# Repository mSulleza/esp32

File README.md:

# ESP32 Smart AC Controller

An IR-based smart controller for air conditioners. An ESP32 **learns** your AC
remote's IR codes, **replays** them to drive the AC (power / mode / temperature /
fan speed), reads **temperature & humidity** from a BME280 sensor, and fires
**schedules** locally even when the internet is down. Everything is connected to
an **AWS IoT Core + Lambda + DynamoDB** backend so you can control and schedule
it from anywhere.

```
   ┌──────────────┐        IR (38 kHz)        ┌──────────────┐
   │  AC Remote   │ ─────capture (learn)────► │              │
   └──────────────┘                           │    ESP32     │
   ┌──────────────┐                           │  Controller  │
   │ Air          │ ◄──────replay (send)───── │              │
   │ Conditioner  │                           │  + BME280    │
   └──────────────┘                           └──────┬───────┘
                                                      │ MQTT / TLS
                                                      ▼
                                    ┌─────────────────────────────────┐
                                    │   AWS IoT Core ── IoT Rules      │
                                    │      │            │              │
                                    │   Lambda  ──  DynamoDB           │
                                    │      │                           │
                                    │   API Gateway (HTTP API) ── App  │
                                    └─────────────────────────────────┘
```

## Repository layout

| Path | What's inside |
|------|---------------|
| `docs/DESIGN.md`   | System architecture, data flow, MQTT topics, data model |
| `docs/HARDWARE.md` | Breadboard/prototype wiring (dev-board + modules) for quick bring-up |
| `hardware/`        | **Orderable integrated PCB**: schematic, PCBA BOM (LCSC), layout + JLCPCB fab/order steps |
| `docs/API.md`      | REST API + MQTT topic + Device Shadow contracts |
| `docs/COST.md`     | Cost breakdown, optimizations, and the billing guardrail |
| `firmware/`        | PlatformIO ESP32 firmware (IR learn/send, sensor, schedules, MQTT) |
| `backend/cdk/`     | AWS CDK infrastructure (IoT Core, Lambda, DynamoDB, API Gateway) |
| `backend/lambdas/` | Lambda function source (API, command publisher, schedule sync) |

## Quick start

1. **Hardware** — build the circuit in [`docs/HARDWARE.md`](docs/HARDWARE.md).
2. **Backend** — `cd backend/cdk && npm install && npx cdk deploy`. Note the
   IoT endpoint and API URL it prints, and download the device certificate.
3. **Firmware** — copy `firmware/src/secrets.example.h` to `secrets.h`, fill in
   Wi-Fi + IoT endpoint + certificates, then `cd firmware && pio run -t upload`.
4. **Learn your remote** — put the device in capture mode (button or API), point
   your AC remote at the receiver, and press each button to store the codes.
5. **Control & schedule** — use the REST API / app to send commands and create
   schedules.

See each `docs/` file for full detail. Status: **reference design + working
skeleton** — protocol decoding for your specific AC may need tuning (see
`docs/DESIGN.md` § "Generic / multi-brand strategy").

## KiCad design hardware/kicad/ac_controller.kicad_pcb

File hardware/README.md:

# Hardware — Integrated PCB (orderable)

This folder is the **manufacturable, integrated board**: a bare
**ESP32-WROOM-32E** with USB-C, USB-UART programming, an on-board 3.3 V
regulator, on-board BME280, an on-board **SMD IR receiver** (to learn your
remote) and an on-board **SMD IR emitter LED** (to send commands to the AC).
**Fully JLCPCB-PCBA assembled** — every part is SMD; the only through-hole pads
are the ESP32 thermal vias (reflowed) and the USB-C connector's anchor legs
(which JLC assembles). Nothing is left for you to hand-solder.

> Trade-off vs. the earlier external-LED design: the IR emitter is now an
> **on-board top-view LED**, so the **board itself must face the AC** (no aimable
> flying lead). That's the cost of full machine assembly.

> The breadboard/prototype wiring in [`../docs/HARDWARE.md`](../docs/HARDWARE.md)
> is the *quick bring-up* version using dev-board + modules. **This** folder is
> the integrated PCB you actually order. The firmware pin map is identical, so
> firmware needs no changes between the two.

## Files

| File | What it is |
|------|------------|
| [`kicad/ac_controller.kicad_pro`](kicad/ac_controller.kicad_pro) | KiCad project (open this) |
| [`kicad/ac_controller.kicad_sch`](kicad/ac_controller.kicad_sch) | **Real, openable KiCad 10 schematic.** ERC-validated: **0 errors** |
| [`kicad/ac_controller.pdf`](kicad/ac_controller.pdf) | Rendered schematic to eyeball without opening KiCad |
| [`kicad/ac_controller.net`](kicad/ac_controller.net) | Exported netlist (connectivity reference) |
| [`kicad/ac_controller.kicad_pcb`](kicad/ac_controller.kicad_pcb) | Board with **all footprints placed** (un-routed starting point; also the source of the 3D render) |
| [`kicad/board3d.png`](kicad/board3d.png) | **3D render** of the populated board |
| [`kicad/gen_schematic.py`](kicad/gen_schematic.py) | Generator for the schematic (reads your KiCad symbol libs) |
| [`kicad/gen_pcb.py`](kicad/gen_pcb.py) | Generator for the placed PCB / 3D render (uses the `pcbnew` Python API) |
| [`SCHEMATIC.md`](SCHEMATIC.md) | Human-readable schematic: every sub-circuit + net-by-net netlist |
| [`BOM.csv`](BOM.csv) | PCBA bill of materials with LCSC part numbers (Basic/Extended flagged) |
| [`LAYOUT.md`](LAYOUT.md) | Stackup, JLCPCB design rules, placement, routing, **Gerber export + ordering steps** |
| [`LAYOUT_AUTOMATION.md`](LAYOUT_AUTOMATION.md) | **Researched + tested** free/headless place-&-route pipeline (pcbnew placer + Freerouting) |
| [`kicad/build_board.py`](kicad/build_board.py) | Heuristic placer: nets the board + clusters parts by subsystem |
| [`kicad/run_pipeline.sh`](kicad/run_pipeline.sh) | One-shot place → DSN → Freerouting → SES → DRC |
| [`kicad/placed.kicad_pcb`](kicad/placed.kicad_pcb) · `placed_top.png` | Subsystem-placed board, **68×42 mm** — fixes the grid layout |
| [`kicad/routed.kicad_pcb`](kicad/routed.kicad_pcb) · `routed_top.png` | **Fully autorouted** (0 unconnected) |
| [`kicad/finished.kicad_pcb`](kicad/finished.kicad_pcb) · `finished_top.png` · `finished_3d.png` | **Finished board**: GND pour + antenna keep-out. **68×42 mm, DRC fully clean (0 of everything)**. |
| [`kicad/finish_board.py`](kicad/finish_board.py) | Adds the GND pour and fills zones |
| [`kicad/ac_controller_gerbers.zip`](kicad/ac_controller_gerbers.zip) | **Gerbers + drill** from the finished board — uploadable to JLCPCB |
| [`kicad/ac_controller_cpl.csv`](kicad/ac_controller_cpl.csv) | **CPL / centroid** placement file for PCBA (pairs with `BOM.csv`) |

### 3D model

`kicad/board3d.png` is a real 3D render (every part uses its KiCad-library 3D
model). The `.kicad_pcb` it came from just has the footprints auto-placed on a
grid — it is **not routed and not sensibly placed yet**. For the *real* board +
its proper 3D view: open the project, **Tools → Update PCB from Schematic** (this
pulls the nets/ratsnest), lay it out per `LAYOUT.md`, then **View → 3D Viewer**
(or re-run `gen_pcb.py` to re-render). Regenerate the render headlessly with:
`kicad-cli pcb render --perspective --quality high -o board3d.png ac_controller.kicad_pcb`.

## Status: schematic is done & verified; layout is the remaining step

The schematic was generated as code and **validated with `kicad-cli` (KiCad
10.0.4): ERC reports 0 errors.** The exported netlist was checked node-by-node —
59 nets, no shorts, the auto-reset cross-couple and I²C address strap are correct.
So you do **not** have to capture the schematic by hand.

What's *intentionally* left for you (it needs the KiCad GUI and can't be done
headlessly): **PCB placement, routing, DRC, and Gerber export.** That's where a
board can go wrong, so it belongs where you can see and check it.

### Workflow to an order

1. **Open** `kicad/ac_controller.kicad_pro` in KiCad. Open the schematic.
   - It uses a compact "net-label" style (each pin carries a global label instead
     of drawn wires) so it's electrically complete but visually spread out —
     rearrange to taste, or just proceed; connectivity is already correct.
   - Run **Tools → Update Symbols from Library** once to clear the 6 cosmetic
     `lib_symbol_mismatch` warnings (artifacts of code-generation).
2. **Create the PCB** (Tools → Update PCB from Schematic). Footprints are already
   assigned (verified against your libraries).
3. **Lay out + route** following [`LAYOUT.md`](LAYOUT.md) — 2-layer; mind the
   antenna keepout, USB pair, and auto-reset transistors.
4. **Run DRC** with the JLCPCB rules in `LAYOUT.md`. Fix violations.
5. **Export** Gerbers + drill, and BOM + CPL (assembly) per `LAYOUT.md`.
6. **Order** at JLCPCB: upload Gerber zip, enable PCB Assembly, upload BOM + CPL,
   review the placement preview, pay.

To re-generate the schematic after editing the design, run
`python3 kicad/gen_schematic.py` (it reads symbols from your KiCad install; set
`KICAD_SYMBOL_DIR` if it's not at the default path), then re-run
`kicad-cli sch erc`.

## Why not ready-made Gerbers?

Gerbers are the *output of a routed board*. The schematic is generated and
machine-verified, but routing + DRC must happen in your KiCad GUI where copper
can actually be checked — shipping blind Gerbers would risk paying for a dead
board (unrouted net, bad USB pair). One spin of layout and you're there.

## ⚠️ Before you order — verify these

- **LCSC part numbers drift / go out of stock.** Re-check every line in `BOM.csv`
  against the live JLCPCB Parts Library at order time; swap any out-of-stock part
  for an equivalent and update the footprint if the package changes. The IR LED
  (D3) is a suggested 1206 940 nm part — pick any in-stock equivalent.
- The **IR receiver (U6) pinout is confirmed** from the IRM-H6XXT datasheet
  (pad 1=GND, 2=GND, 3=OUT, 4=Vcc) and wired correctly.
- **Prefer JLCPCB "Basic" parts** (no per-part loading fee). Extended parts cost
  ~$3 setup each — the BOM flags which is which so you can minimise that.
- Order **one** board first, validate (especially the IR learn function), then
  order a batch.

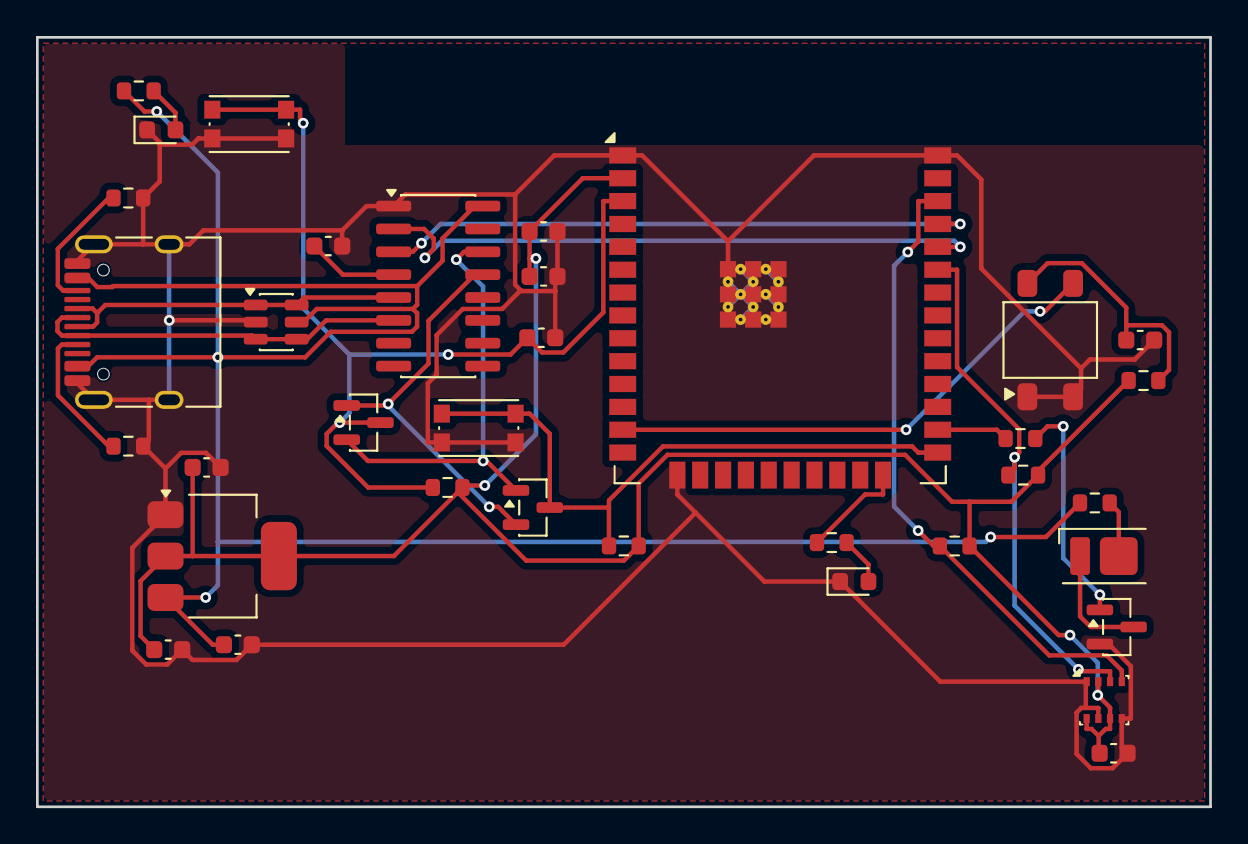
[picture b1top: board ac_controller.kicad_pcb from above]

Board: 2 copper layers, 65.2 x 42.7 mm, 35 parts (0 on the bottom side), 25 nets.

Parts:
C1, C3, C4, C5, C6, C7, C8: C_0603_1608Metric
C_EN: C_0603_1608Metric
C_irrx: C_0603_1608Metric
D1, D2: LED_0603_1608Metric
D3: LED_Everlight-SMD3528_3.5x2.8mm_67-21ST
J1: USB_C_Receptacle_HRO_TYPE-C-31-M-12
Q1, Q2, Q3: SOT-23
R_CC1, R_CC2: R_0603_1608Metric
R_EN: R_0603_1608Metric
R_IO0: R_0603_1608Metric
R_SCL: R_0603_1608Metric
R_SDA: R_0603_1608Metric
R_base: R_0603_1608Metric
R_irrx: R_0603_1608Metric
R_led, R_led2: R_0603_1608Metric
R_pwr: R_0603_1608Metric
SW1, SW2: SW_Push_1P1T_NO_CK_KMR2
U1: SOT-23-6
U2: SOT-223-3_TabPin2
U3: SOIC-16_3.9x9.9mm_P1.27mm
U4: ESP32-WROOM-32E
U5: Bosch_LGA-8_2.5x2.5mm_P0.65mm_ClockwisePinNumberi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; Bosch_LGA-8_2.5x2.5mm_P0.65mm_ClockwisePinNumbering
U6: Everlight_IRM-H6xxT

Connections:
+3V3: C3.1, C4.1, C6.1, C7.1, C8.1, R_EN.2, R_IO0.2, R_SCL.2, R_SDA.2, R_irrx.1, U2.2, U4.2, U5.2, U5.6, U5.8
+5V: C1.1, J1.A4, J1.A9, J1.B4, J1.B9, R_led.1, R_pwr.1, U1.5, U2.3, U3.16
CC1: J1.A5, R_CC1.1
CC2: J1.B5, R_CC2.1
DTR: Q1.2, Q2.1, U3.13
EN: C_EN.1, Q2.3, R_EN.1, SW1.1, U4.3
GND: C1.2, C3.2, C4.2, C5.2, C6.2, C7.2, C8.2, C_EN.2, C_irrx.2, D1.1, D2.1, J1.A1, J1.A12, J1.B1, J1.B12, J1.SH, Q3.2, R_CC1.2, R_CC2.2, SW1.2, SW2.2, U1.2, U2.1, U3.1, U4.1, U4.15, U4.38, U4.39, U5.1, U5.5, U5.7, U6.1, U6.2
I2C_SCL: R_SCL.1, U4.36, U5.4
I2C_SDA: R_SDA.1, U4.33, U5.3
IO0: Q1.3, R_IO0.1, SW2.1, U4.25
IRRX_VCC: C_irrx.1, R_irrx.2, U6.4
IRTX_BASE: Q3.1, R_base.2
IR_LED_A: D3.2, R_led.2
IR_LED_K: D3.1, Q3.3
IR_RX: U4.13, U6.3
IR_TX_GATE: R_base.1, U4.26
LED1A: D1.2, R_pwr.2
LED2A: D2.2, R_led2.2
RTS: Q1.1, Q2.2, U3.14
STATUS_LED: R_led2.1, U4.24
UART_RX: U3.2, U4.34
UART_TX: U3.3, U4.35
USB_DM: J1.A7, J1.B7, U1.3, U1.4, U3.6
USB_DP: J1.A6, J1.B6, U1.1, U1.6, U3.5
VREG3: C5.1, U3.4

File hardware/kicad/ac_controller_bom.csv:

Comment,Designator,Footprint,LCSC Part #
ESP32-WROOM-32E,U4,RF_Module:ESP32-WROOM-32E,C701341
CH340C,U3,Package_SO:SOIC-16_3.9x9.9mm_P1.27mm,C84681
AMS1117-3.3,U2,Package_TO_SOT_SMD:SOT-223-3_TabPin2,C6186
USBLC6-2SC6,U1,Package_TO_SOT_SMD:SOT-23-6,C7519
BME280,U5,Package_LGA:Bosch_LGA-8_2.5x2.5mm_P0.65mm_ClockwisePinNumbering,C92489
IR-Receiver-38kHz,U6,OptoDevice:Everlight_IRM-H6xxT,C91447
USB-C-16P,J1,Connector_USB:USB_C_Receptacle_HRO_TYPE-C-31-M-12,C165948
IR-LED-940nm,D3,LED_SMD:LED_Everlight-SMD3528_3.5x2.8mm_67-21ST,C60109
MMBT3904,"Q1,Q2,Q3",Package_TO_SOT_SMD:SOT-23,C20526
LED-Red,"D1,D2",LED_SMD:LED_0603_1608Metric,C2286
SW-Tact-SMD,"SW1,SW2",Button_Switch_SMD:SW_Push_1P1T_NO_CK_KMR2,C318884
10uF,"C1,C3,C7",Capacitor_SMD:C_0603_1608Metric,C19702
100nF,"C4,C5,C6,C8",Capacitor_SMD:C_0603_1608Metric,C14663
1uF,C_EN,Capacitor_SMD:C_0603_1608Metric,C15849
4.7uF,C_irrx,Capacitor_SMD:C_0603_1608Metric,C19666
10k,"R_EN,R_IO0",Resistor_SMD:R_0603_1608Metric,C25804
4.7k,"R_SCL,R_SDA",Resistor_SMD:R_0603_1608Metric,C23162
5.1k,"R_CC1,R_CC2",Resistor_SMD:R_0603_1608Metric,C23186
1k,"R_base,R_pwr",Resistor_SMD:R_0603_1608Metric,C21190
100,R_irrx,Resistor_SMD:R_0603_1608Metric,C22775
47,R_led,Resistor_SMD:R_0603_1608Metric,C23182
330,R_led2,Resistor_SMD:R_0603_1608Metric,C23138

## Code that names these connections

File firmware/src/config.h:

// Compile-time configuration: pin map, timing, topics.
#pragma once

// ---- GPIO pin map (see docs/HARDWARE.md) ----
#define PIN_IR_TX        4    // RMT-capable; drives transistor base via 1k
#define PIN_IR_RX        14   // IR receiver OUT
#define PIN_I2C_SDA      21
#define PIN_I2C_SCL      22
#define PIN_STATUS_LED   2    // on-board LED
#define PIN_CAPTURE_BTN  0    // optional push-to-GND learn button (boot strap)

// ---- SHT40 (temp + humidity, fixed I2C address) ----
#define SHT40_ADDR  0x44

// ---- Timing ----
// Cost note: every telemetry publish is 1 IoT message + 1 DynamoDB write. Room
// temp/humidity change slowly, so we sample often but only *publish* on a
// meaningful change (delta) or a periodic heartbeat. This cuts cloud volume
// ~5-10x vs publishing every sample. See docs/COST.md.
#define SENSOR_SAMPLE_MS        30000UL   // how often we read the SHT40
#define TELEMETRY_HEARTBEAT_MS  600000UL  // force a publish at least every 10 min
#define TELEMETRY_DELTA_TEMP    0.3f      // °C change that triggers a publish
#define TELEMETRY_DELTA_HUM     2.0f      // %RH change that triggers a publish
#define SCHEDULE_TICK_MS        15000UL   // how often the schedule engine evaluates
#define MQTT_RECONNECT_MS       5000UL
#define CAPTURE_DEFAULT_TIMEOUT 30        // seconds in learn mode before auto-exit

// ---- Time / NTP ----
#define NTP_SERVER_1   "pool.ntp.org"
#define NTP_SERVER_2   "time.nist.gov"
// POSIX TZ string. Examples: "SGT-8" (Singapore), "GMT0BST,M3.5.0/1,M10.5.0"
// (UK), "EST5EDT,M3.2.0,M11.1.0" (US Eastern). Change to your zone.
#define TZ_STRING      "SGT-8"

// ---- IR capture buffer ----
#define IR_CAPTURE_BUFFER_SIZE  1024  // raw timing entries; AC frames are long
#define IR_CAPTURE_TIMEOUT      50    // ms idle gap that ends a capture
#define IR_MIN_UNKNOWN_SIZE     12

// ---- MQTT topics (printf templates, %s = DEVICE_ID) ----
#define TOPIC_TELEMETRY   "ac/%s/telemetry"
#define TOPIC_STATE       "ac/%s/state"
#define TOPIC_CAPTURED    "ac/%s/captured"
#define TOPIC_COMMAND     "ac/%s/command"
#define TOPIC_SCHEDULES   "ac/%s/schedules"
#define TOPIC_ACK         "ac/%s/ack"

// Setpoint range accepted from the cloud (most IRremoteESP8266 AC protocols
// support at least 16-30 °C). Keep in sync with TEMP_MIN_C / TEMP_MAX_C in
// backend/lambdas/api/index.mjs.
#define AC_MIN_TEMP_C   16
#define AC_MAX_TEMP_C   30

#define FW_VERSION   "1.0.0"
#define MAX_SCHEDULES   32
#define MAX_RAW_CODES   24
